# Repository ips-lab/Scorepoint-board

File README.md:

# Scorepoint-board
Ping Pong scoreboard controlled with an Arduino Mega. Connects to server with NodeMCU and reads buttons with X-Bees.  

- NodeMCU was programmed with arduino, using https://github.com/esp8266/Arduino
- X-Bees were programmed using XCTU software. 
- The PCBs of digits can be found in the ScorePointDigits folder. 
- The matrices used: https://www.tindie.com/products/hnhoan/led-32x8-matrix-display-board-for-arduino-arm/

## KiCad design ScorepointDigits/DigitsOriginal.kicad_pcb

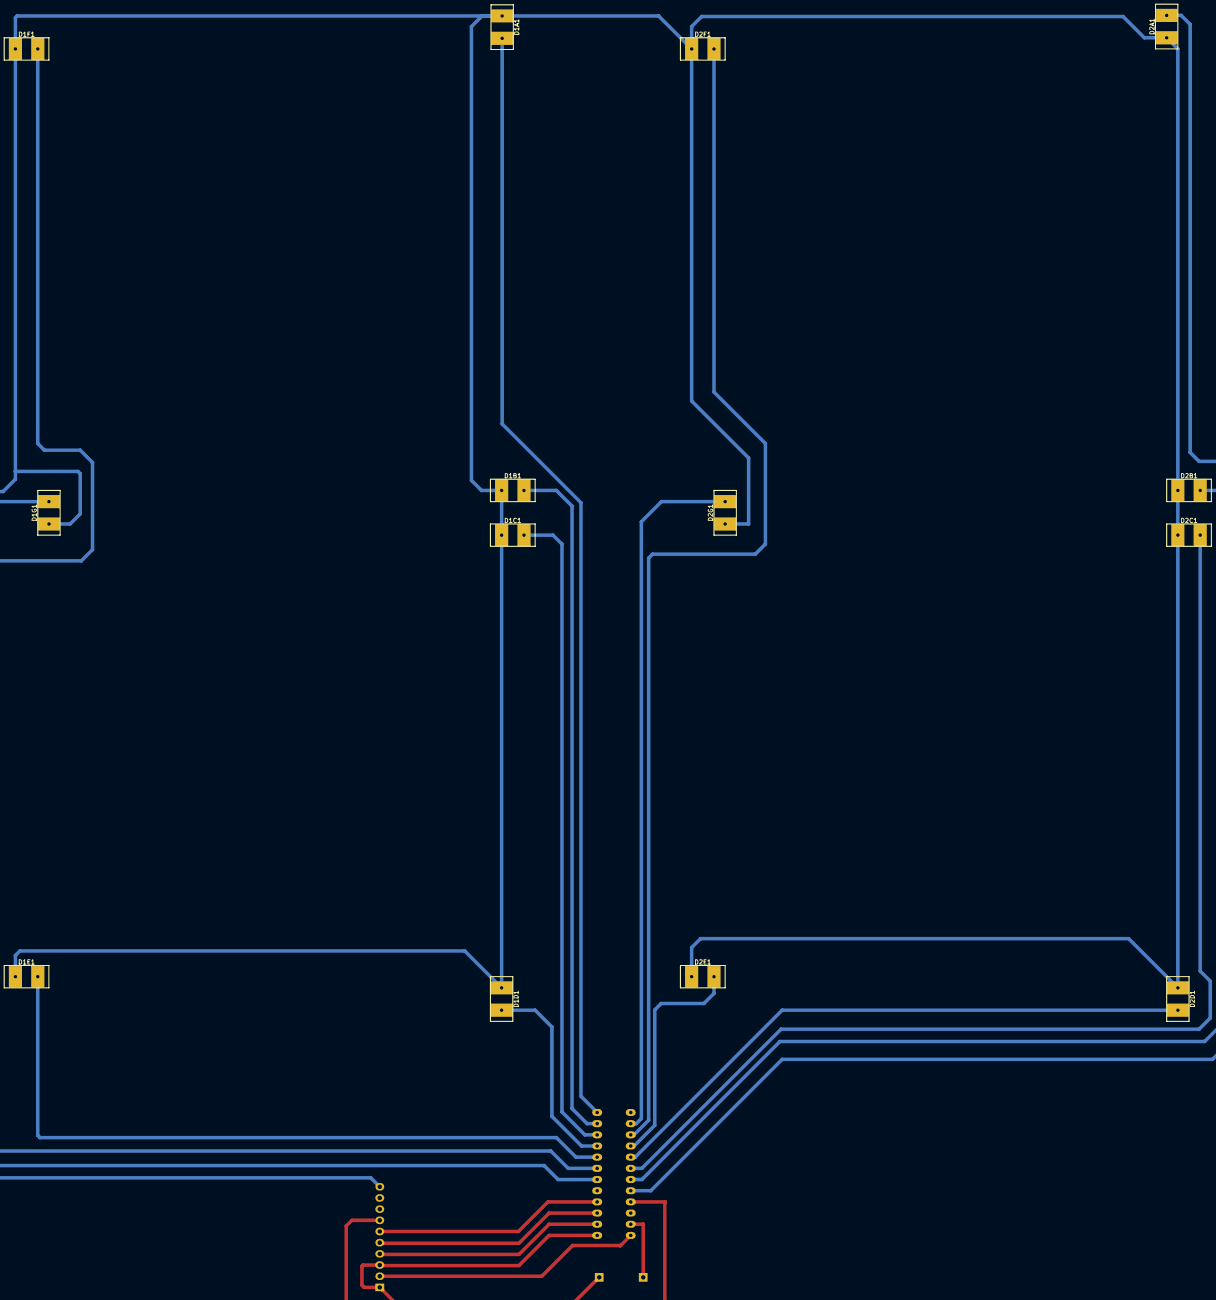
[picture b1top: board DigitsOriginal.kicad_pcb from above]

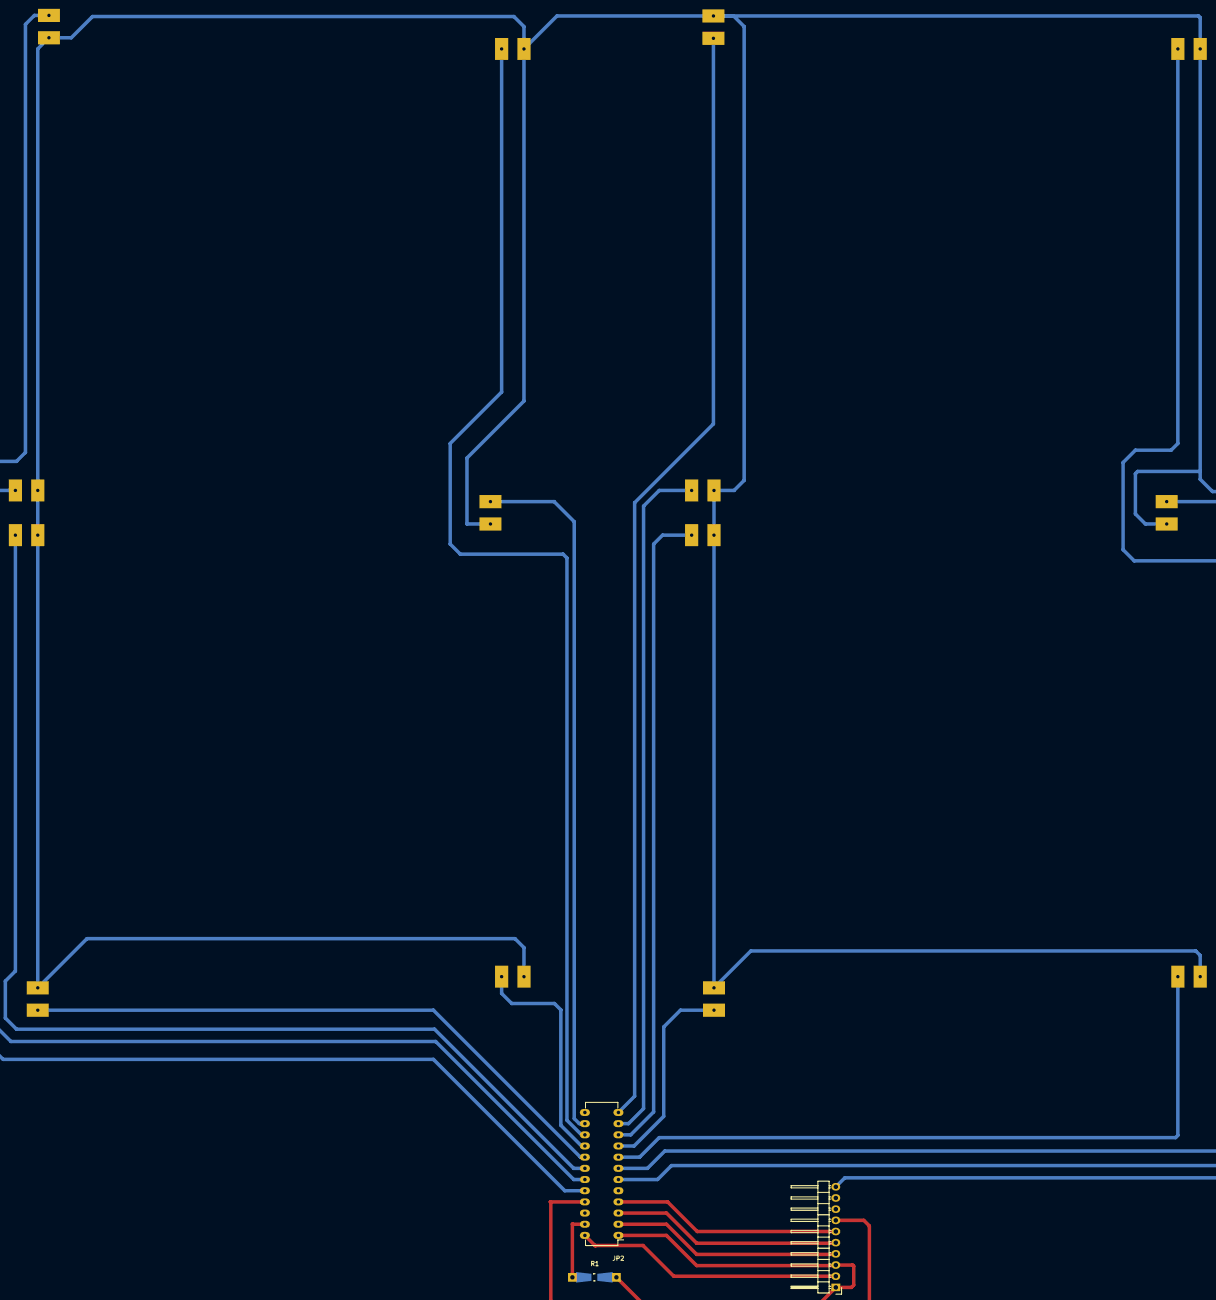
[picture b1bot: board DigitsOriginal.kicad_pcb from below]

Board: 2 copper layers, 17 parts (3 on the bottom side), 22 nets.

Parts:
D1A1, D1B1, D1C1, D1D1, D1E1, D1F1, D1G1, D2A1, D2B1, D2C1, D2D1, D2E1, D2F1, D2G1: LEDStrip; LedStrip
JP1: PINHD-1X10; Pin_Header_Angled_1x10
JP2: ICsocket; DIP-24_W7.62mm_LongPads
R1: 560; Resistor_SMD+THTuniversal_0805to1206_RM10_HandSoldering

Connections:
/5V: JP1.2, JP2.24
/12V: D1A1.+, D1B1.+, D1C1.+, D1D1.+, D1E1.+, D1F1.+, D1G1.+, D2A1.+, D2B1.+, D2C1.+, D2D1.+, D2E1.+, D2F1.+, D2G1.+, JP1.10
/CLK: JP1.5, JP2.3
/GND: JP1.1, JP1.3, JP2.1, R1.2
/LE: JP1.6, JP2.4
/OE: JP1.7, JP2.21
/SDI: JP1.4, JP2.2
/d1a: D1A1.-, JP2.12
/d1b: D1B1.-, JP2.11
/d1c: D1C1.-, JP2.10
/d1d: D1D1.-, JP2.9
/d1e: D1E1.-, JP2.8
/d1f: D1F1.-, JP2.7
/d1g: D1G1.-, JP2.6
/d2a: D2A1.-, JP2.20
/d2b: D2B1.-, JP2.19
/d2c: D2C1.-, JP2.18
/d2d: D2D1.-, JP2.17
/d2e: D2E1.-, JP2.16
/d2f: D2F1.-, JP2.15
/d2g: D2G1.-, JP2.14
unnamed: JP2.23, R1.1

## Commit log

2017-05-13 Create Manual
2017-05-15 Add files via upload
    PCB for digits.
2017-05-15 Create web-services
